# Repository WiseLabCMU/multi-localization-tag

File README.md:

# multi-localization-tag
Hardware design for localization tag supporting UWB, Glitter, Lighthouse

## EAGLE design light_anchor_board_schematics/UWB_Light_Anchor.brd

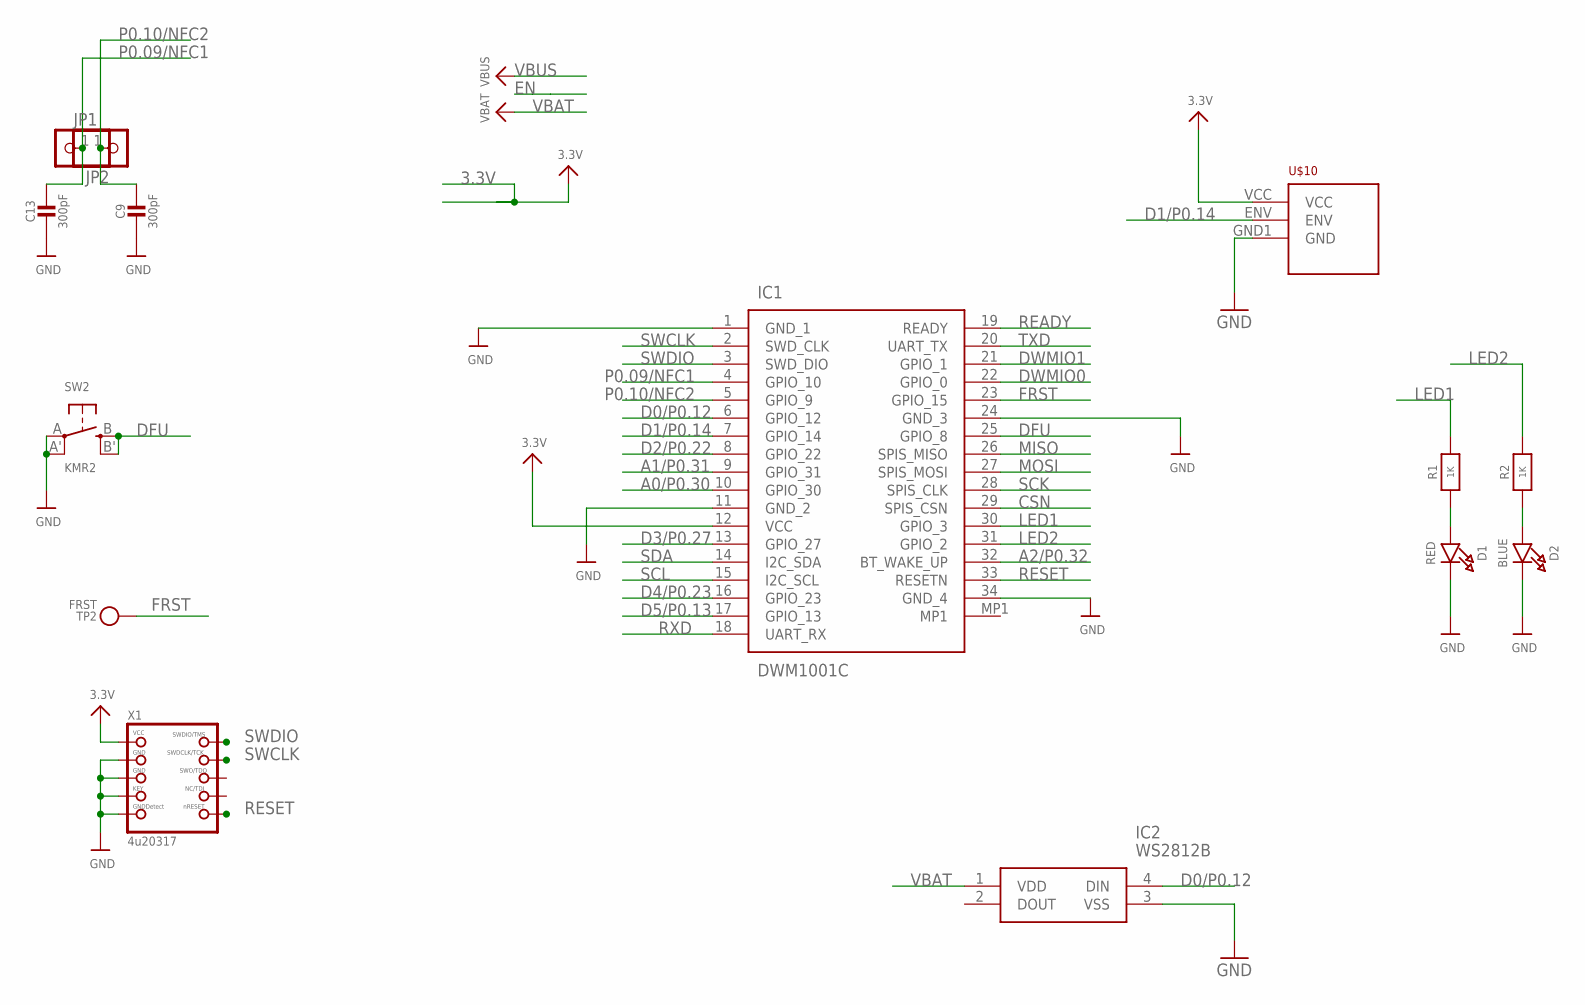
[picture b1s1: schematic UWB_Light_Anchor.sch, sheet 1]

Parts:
C9, C13: 300pF; _0603MP
D1: RED; CHIPLED_0805_NOOUTLINE
D2: BLUE; CHIPLED_0805_NOOUTLINE
IC1: DWM1001C
IC2: WS2812B
JP1, JP2: HEADER-1X12MM; 1X01_2MM
R1, R2: 1K; 0603-NO
SW2: KMR2; BTN_KMR2_4.6X2.8
TP2: FRST; PAD-1.5X2.0
U$10: TS3633-CM1
X1: 4u20317; 2X05_1.27MM_BOX_POSTS

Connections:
3.3V: IC1.12 (VCC), U$10.VCC, X1.1 (VCC); also elsewhere on the board
A0/P0.30: IC1.10 (GPIO_30); also elsewhere on the board
A1/P0.31: IC1.9 (GPIO_31)
A2/P0.32: IC1.32 (BT_WAKE_UP)
CSN: IC1.29 (SPIS_CSN)
D0/P0.12: IC1.6 (GPIO_12), IC2.4 (DIN)
D1/P0.14: IC1.7 (GPIO_14), U$10.ENV
D2/P0.22: IC1.8 (GPIO_22)
D3/P0.27: IC1.13 (GPIO_27)
D4/P0.23: IC1.16 (GPIO_23)
D5/P0.13: IC1.17 (GPIO_13)
DFU: IC1.25 (GPIO_8), SW2.B (S), SW2.B' (S1)
DWMIO0: IC1.22 (GPIO_0)
DWMIO1: IC1.21 (GPIO_1)
FRST: IC1.23 (GPIO_15), TP2.P$1
GND: C9.2, C13.2, D1.C, D2.C, IC1.1 (GND_1), IC1.11 (GND_2), IC1.24 (GND_3), IC1.34 (GND_4), IC2.3 (VSS), SW2.A, SW2.A' (P1), U$10.GND1 (GND), X1.3 (GND), X1.5 (GND), X1.7 (KEY), X1.9 (GNDDETECT); also elsewhere on the board
LED1: IC1.30 (GPIO_3), R1.2
LED2: IC1.31 (GPIO_2), R2.2
MISO: IC1.26 (SPIS_MISO)
MOSI: IC1.27 (SPIS_MOSI)
unnamed: D1.A, R1.1
unnamed: D2.A, R2.1
P0.09/NFC1: C13.1, IC1.4 (GPIO_10), JP2.1
P0.10/NFC2: C9.1, IC1.5 (GPIO_9), JP1.1
READY: IC1.19 (READY)
RESET: IC1.33 (RESETN), X1.10 (NRESET); also elsewhere on the board
RXD: IC1.18 (UART_RX); also elsewhere on the board
SCK: IC1.28 (SPIS_CLK)
SCL: IC1.15 (I2C_SCL)
SDA: IC1.14 (I2C_SDA)
SWCLK: IC1.2 (SWD_CLK), X1.4 (SWDCLK)
SWDIO: IC1.3 (SWD_DIO), X1.2 (SWDIO)
TXD: IC1.20 (UART_TX); also elsewhere on the board
VBAT: IC2.1 (VDD); also elsewhere on the board

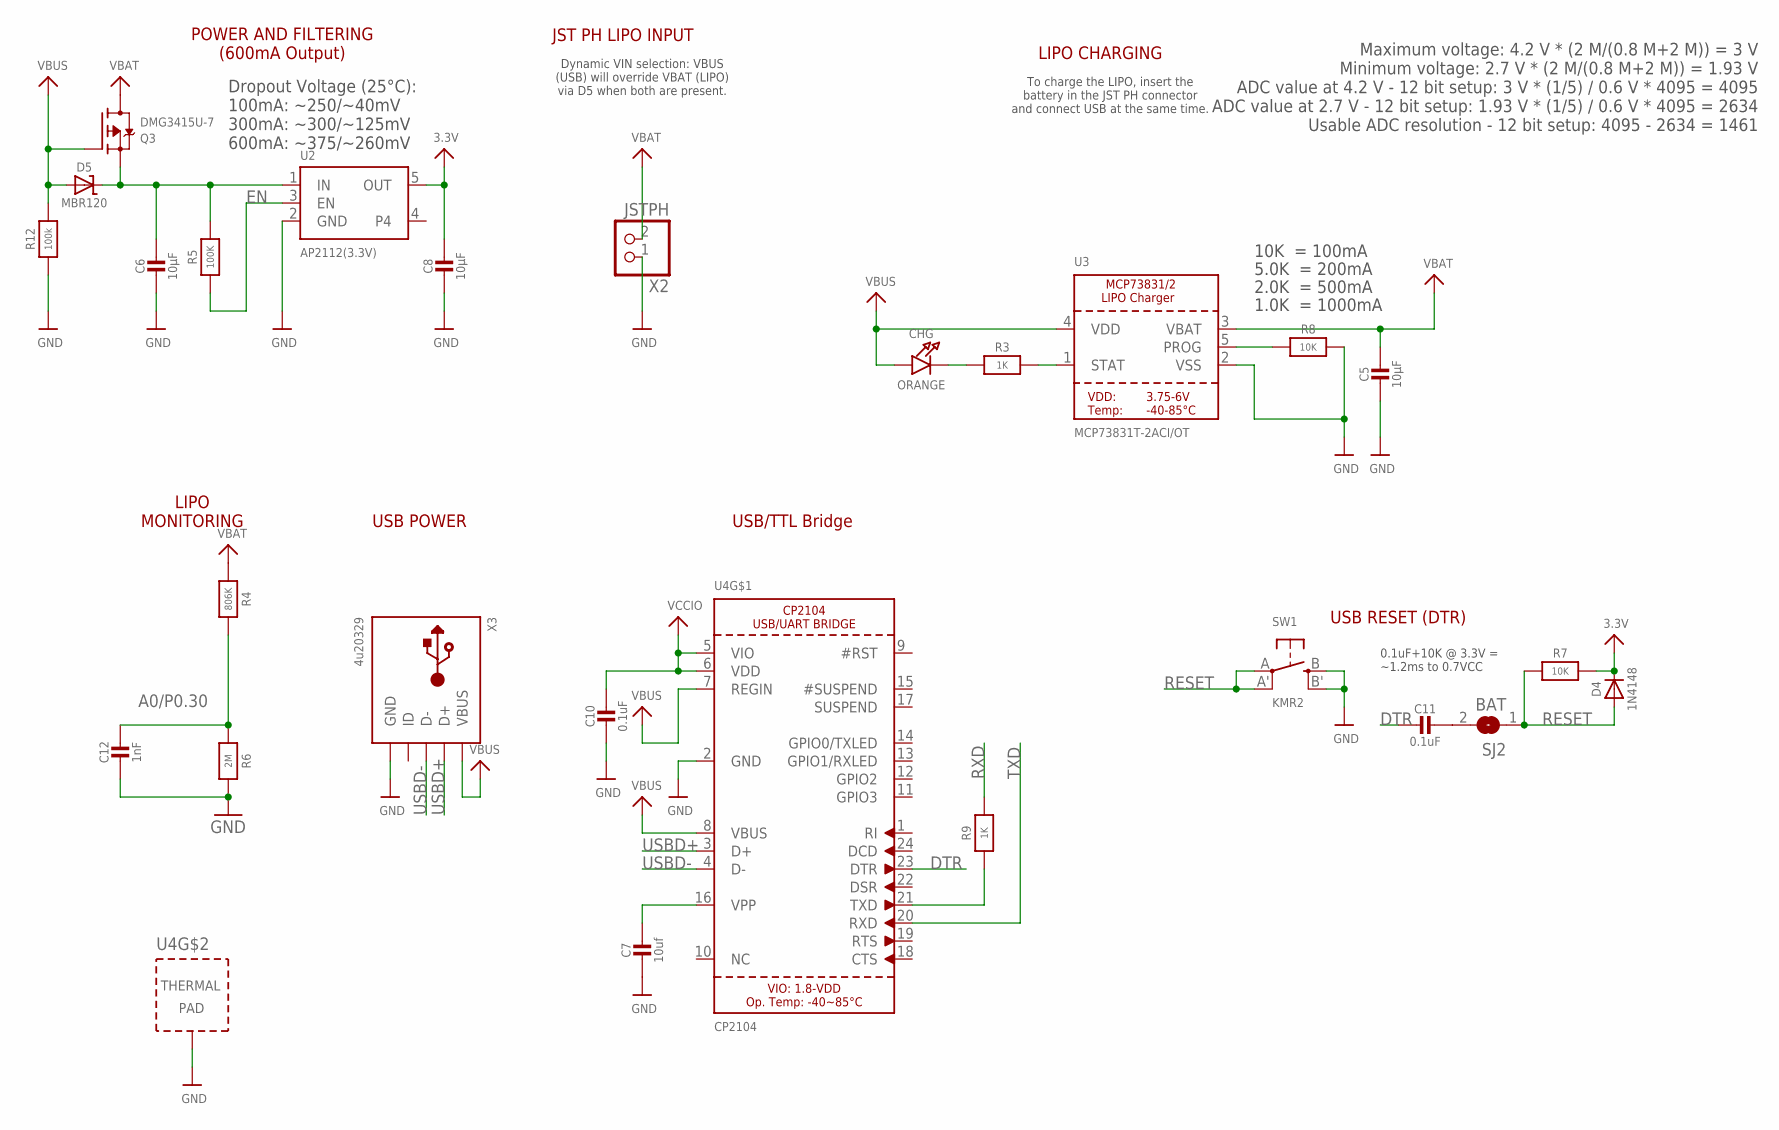
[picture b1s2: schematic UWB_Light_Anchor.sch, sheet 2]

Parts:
C5, C6, C8: 10µF; 0805-NO
C7: 10uf; 0805-NO
C10, C11: 0.1uF; 0603-NO
C12: 1nF; 0603-NO
CHG: ORANGE; CHIPLED_0805_NOOUTLINE
D4: 1N4148; SOD-323
D5: MBR120; SOD-123
Q3: DMG3415U-7; SOT23-R
R3, R9: 1K; 0603-NO
R4: 806K; 0603-NO
R5: 100K; 0603-NO
R6: 2M; 0603-NO
R7, R8: 10K; 0603-NO
R12: 100k; 0603-NO
SJ2: BAT; SOLDERJUMPER_CLOSEDWIRE
SW1: KMR2; BTN_KMR2_4.6X2.8
U2: AP2112(3.3V); SOT23-5
U3: MCP73831T-2ACI/OT; SOT23-5
U4: CP2104; QFN24_4MM_SMSC
X2: JSTPH; JSTPH2
X3: 4u20329; 4UCONN_20329_V2

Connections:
3.3V: C8.1, D4.C, R7.2, U2.5 (OUT); also elsewhere on the board
A0/P0.30: C12.1, R4.2, R6.1; also elsewhere on the board
DTR: C11.2, U4.23 (DTR)
EN: R5.1, U2.3 (EN)
GND: C5.2, C6.2, C7.2, C8.2, C10.2, C12.2, R6.2, R8.2, R12.1, SW1.B (S), SW1.B' (S1), U2.2 (GND), U3.2 (VSS), U4.2 (GND), U4.THERM (TP), X2.1, X3.BASE@1 (GND), X3.BASE@2 (GND), X3.GND, X3.SPRT@1 (GND), X3.SPRT@2 (GND), X3.SPRT@3 (GND), X3.SPRT@4 (GND); also elsewhere on the board
unnamed: CHG.C, R3.1
unnamed: R3.2, U3.1 (STAT)
unnamed: R8.1, U3.5 (PROG)
unnamed: R9.1, U4.21 (TXD)
unnamed: C11.1, SJ2.2
unnamed: C7.1, U4.16 (VPP)
RESET: D4.A, R7.1, SJ2.1, SW1.A, SW1.A' (P1); also elsewhere on the board
RXD: R9.2; also elsewhere on the board
TXD: U4.20 (RXD); also elsewhere on the board
USBD+: U4.3 (D+), X3.D+
USBD-: U4.4 (D-), X3.D-
VBAT: C5.1, Q3.3 (D), R4.1, U3.3 (VBAT), X2.2; also elsewhere on the board
VBUS: CHG.A, D5.A, Q3.1 (G), R12.2, U3.4 (VDD), U4.7 (REGIN), U4.8 (VBUS), X3.VBUS
VCCIO: C10.1, U4.5 (VIO), U4.6 (VDD)
VIN: C6.1, D5.C, Q3.2 (S), R5.2, U2.1 (IN)

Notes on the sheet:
10K = 100mA
5.0K = 200mA
2.0K = 500mA
1.0K = 1000mA
LIPO CHARGING
LIPO MONITORING
To charge the LIPO, insert the battery in the JST PH connector and connect USB at the same time.
POWER AND FILTERING (600mA Output)
JST PH LIPO INPUT
Dynamic VIN selection: VBUS (USB) will override VBAT (LIPO) via D5 when both are present.
Dropout Voltage (25°C): 100mA: ~250/~40mV 300mA: ~300/~125mV 600mA: ~375/~260mV
USB POWER
USB/TTL Bridge
Maximum voltage: 4.2 V * (2 M/(0.8 M+2 M)) = 3 V Minimum voltage: 2.7 V * (2 M/(0.8 M+2 M)) = 1.93 V ADC value at 4.2 V - 12 bit setup: 3 V * (1/5) / 0.6 V * 4095 = 4095 ADC value at 2.7 V - 12 bit setup: 1.93 V * (1/5) / 0.6 V * 4095 = 2634 Usable ADC resolution - 12 bit setup: 4095 - 2634 = 1461
USB RESET (DTR)
0.1uF+10K @ 3.3V = ~1.2ms to 0.7VCC

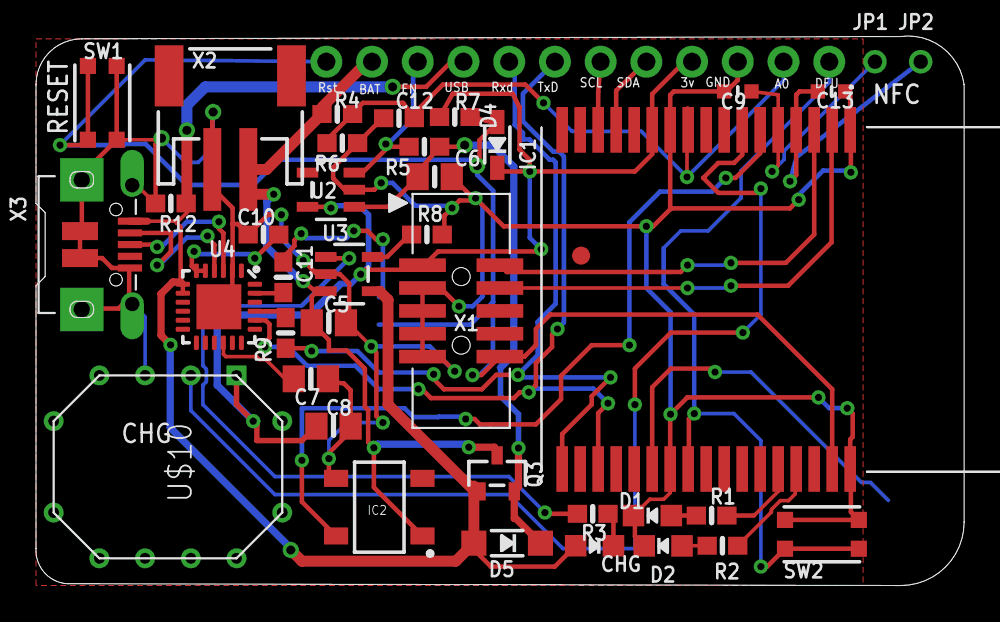
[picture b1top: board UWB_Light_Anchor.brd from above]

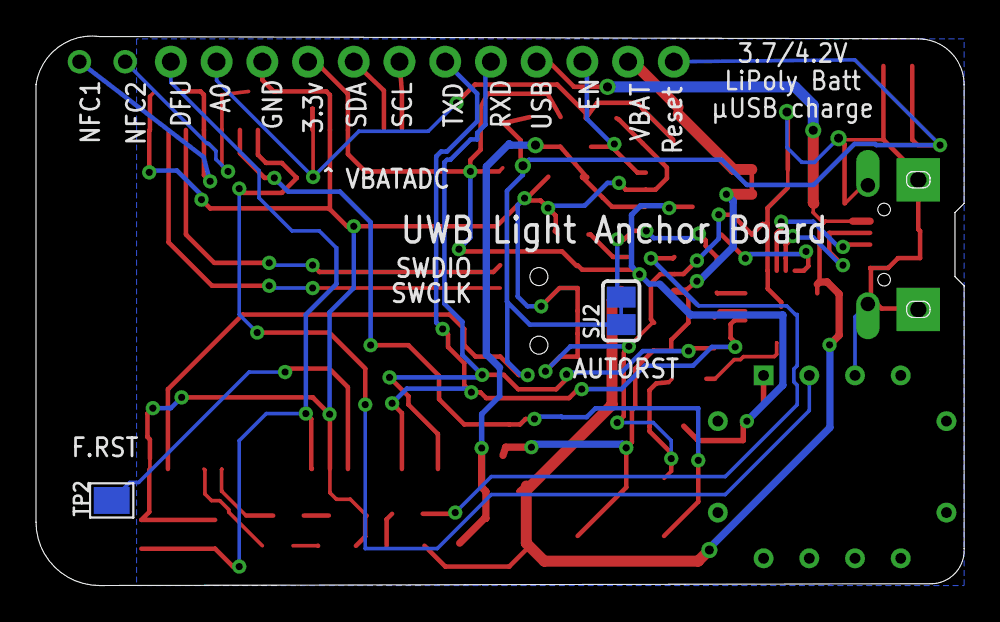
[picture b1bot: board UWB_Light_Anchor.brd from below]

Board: 2 copper layers, 51.6 x 30.5 mm, 40 parts (2 on the bottom side), 32 nets.

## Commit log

2020-01-31 Initial library and schematic files

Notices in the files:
parts and their libraries:
microbuilder: This work is placed in the public domain, and may be freely used for commercial and non-commercial work with the following conditions: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
